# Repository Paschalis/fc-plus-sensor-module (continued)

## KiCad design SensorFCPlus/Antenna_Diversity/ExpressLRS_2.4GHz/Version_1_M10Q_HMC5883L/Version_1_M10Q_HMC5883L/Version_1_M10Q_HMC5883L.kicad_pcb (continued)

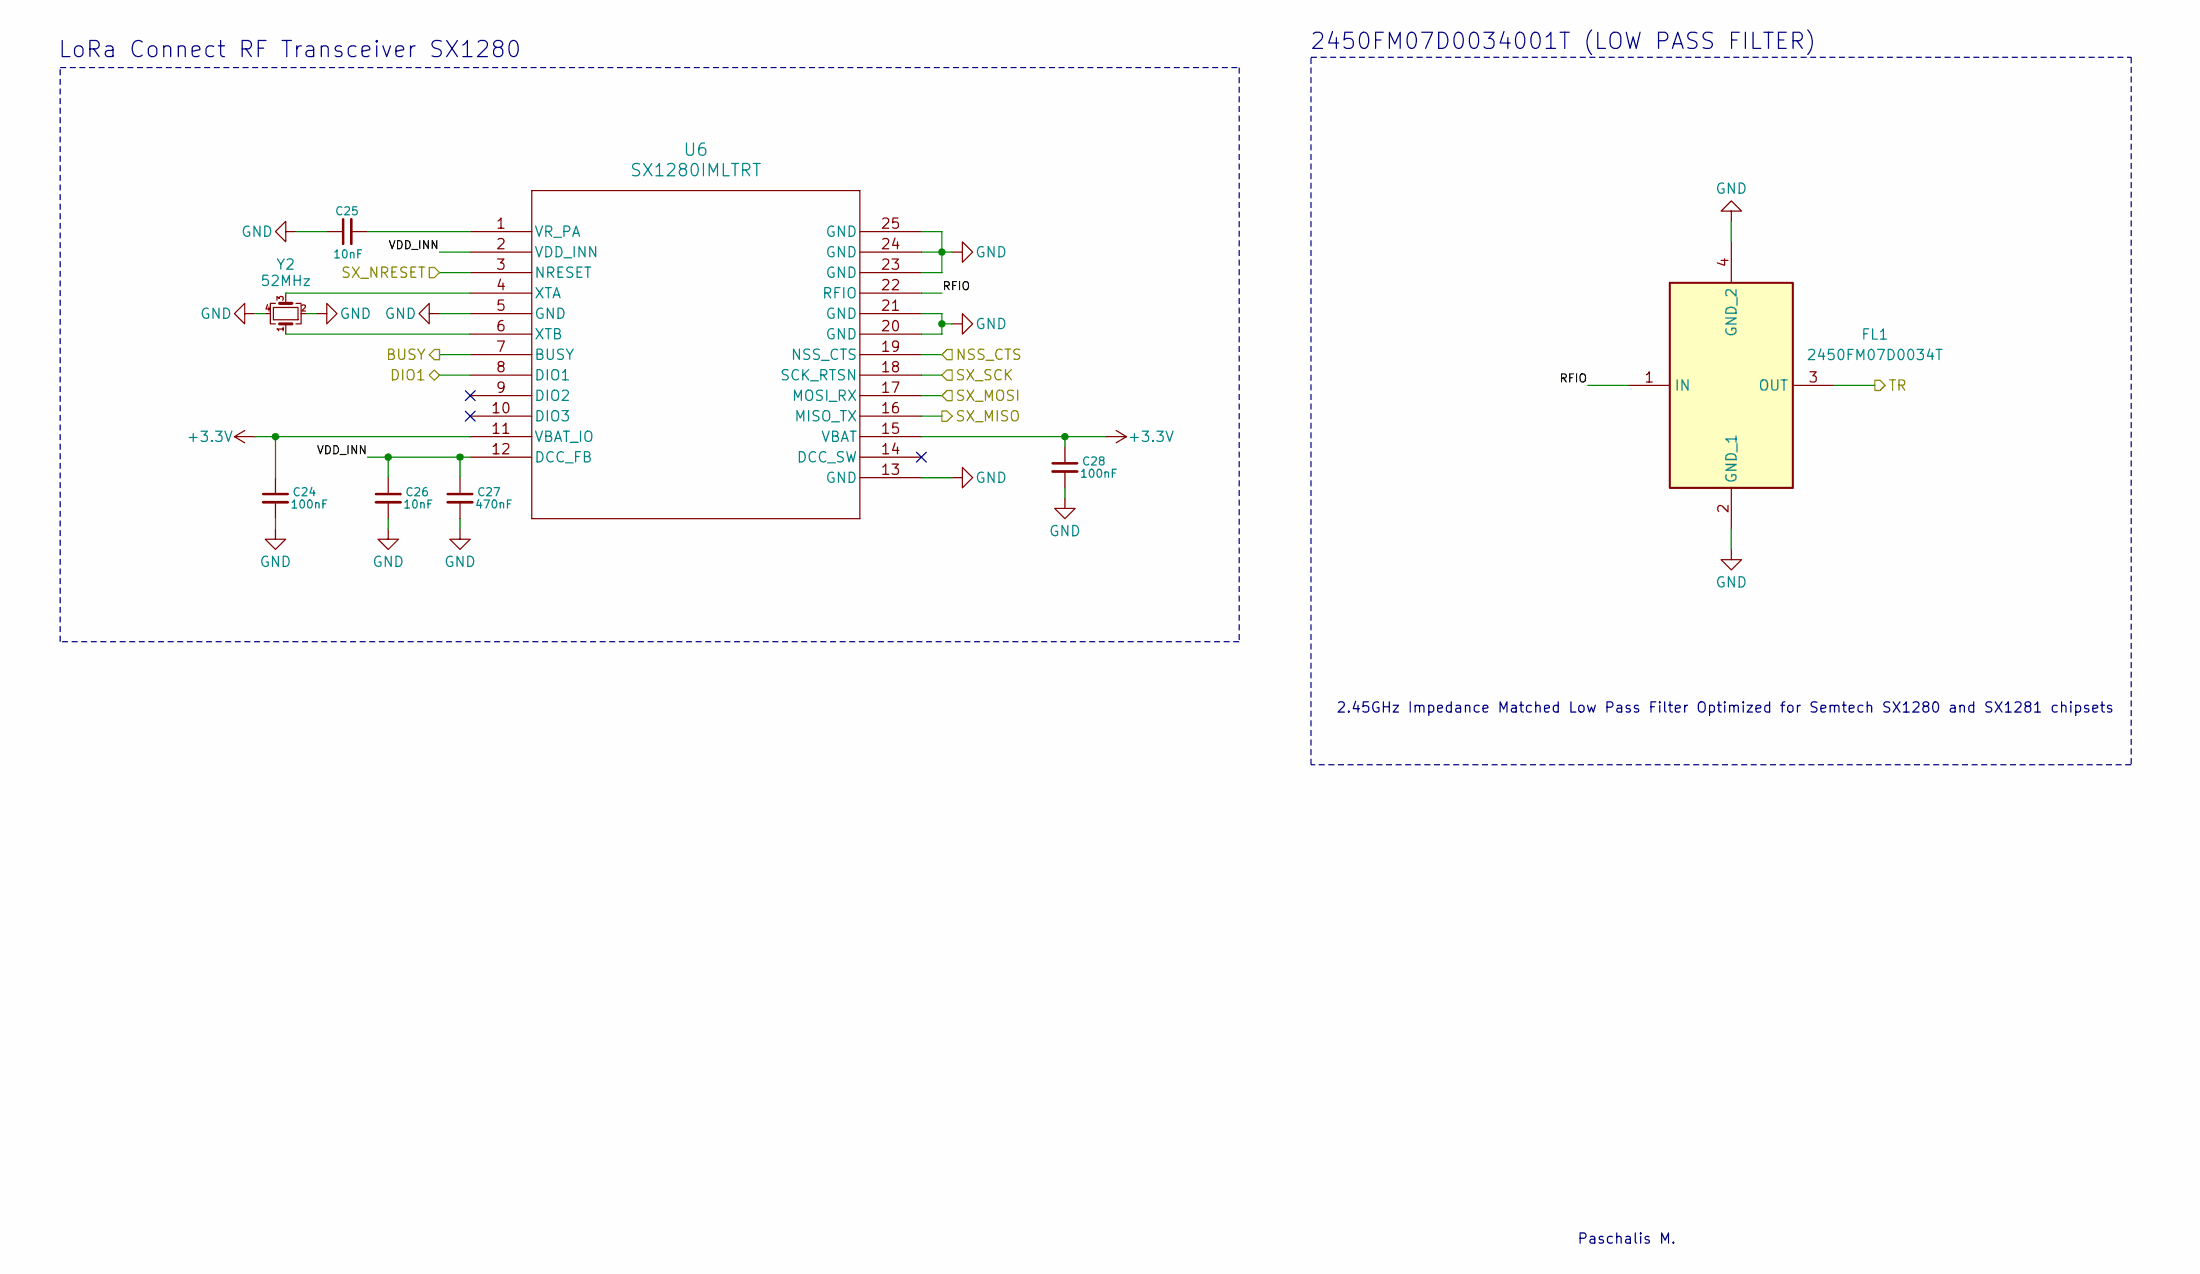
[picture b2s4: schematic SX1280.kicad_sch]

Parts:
C24, C28: 100nF; C_0805_2012Metric_Pad1.18x1.45mm_HandSolder
C25, C26: 10nF; C_0805_2012Metric_Pad1.18x1.45mm_HandSolder
C27: 470nF; C_0805_2012Metric_Pad1.18x1.45mm_HandSolder
FL1: 2450FM07D0034T; Mouser Part Number 609-2450FM07D0034T
U6: SX1280IMLTRT; QFN24_4X4_SEM
Y2: 52MHz; Crystal_SMD_2016-4Pin_2.0x1.6mm

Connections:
+3.3V: C24.1, C28.1, U6.11 (VBAT_IO), U6.15 (VBAT); also elsewhere on the board
/ESP8285/BUSY: U6.7 (BUSY); also elsewhere on the board
/ESP8285/DIO1: U6.8 (DIO1); also elsewhere on the board
/ESP8285/NSS_CTS: U6.19 (NSS_CTS); also elsewhere on the board
/ESP8285/SX_MISO: U6.16 (MISO_TX); also elsewhere on the board
/ESP8285/SX_MOSI: U6.17 (MOSI_RX); also elsewhere on the board
/ESP8285/SX_NRESET: U6.3 (NRESET); also elsewhere on the board
/ESP8285/SX_SCK: U6.18 (SCK_RTSN); also elsewhere on the board
/SE2431L/TR: FL1.3 (OUT); also elsewhere on the board
/SX1280/RFIO: FL1.1 (IN), U6.22 (RFIO)
/SX1280/VDD_INN: C26.1, C27.1, U6.2 (VDD_INN), U6.12 (DCC_FB)
GND: C24.2, C25.1, C26.2, C27.2, C28.2, FL1.2 (GND_1), FL1.4 (GND_2), U6.5 (GND), U6.13 (GND), U6.20 (GND), U6.21 (GND), U6.23 (GND), U6.24 (GND), U6.25 (GND), Y2.2, Y2.4; also elsewhere on the board
unnamed: C25.2, U6.1 (VR_PA)
unnamed: U6.4 (XTA), Y2.3
unnamed: U6.6 (XTB), Y2.1

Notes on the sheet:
2450FM07D0034001T (LOW PASS FILTER)
LoRa Connect RF Transceiver SX1280
Paschalis M.
2.45GHz Impedance Matched Low Pass Filter Optimized for Semtech SX1280 and SX1281 chipsets

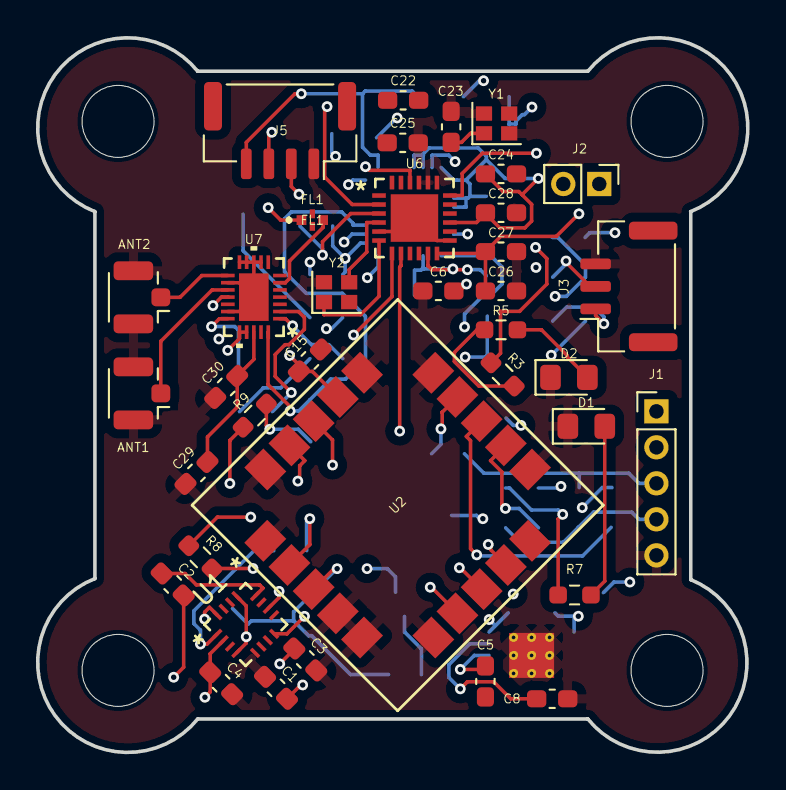
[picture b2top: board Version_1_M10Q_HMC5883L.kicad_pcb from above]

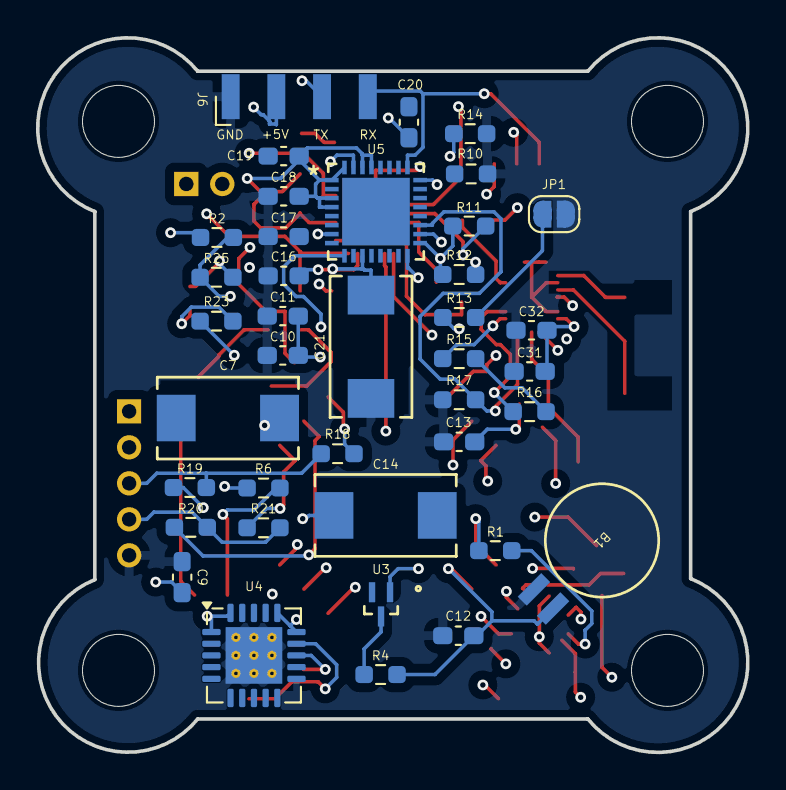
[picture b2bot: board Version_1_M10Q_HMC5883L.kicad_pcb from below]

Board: 4 copper layers, 39.4 x 39.7 mm, 80 parts (39 on the bottom side), 57 nets.

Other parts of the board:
hole1, hole2, hole3, hole4: MountingHole_4mm

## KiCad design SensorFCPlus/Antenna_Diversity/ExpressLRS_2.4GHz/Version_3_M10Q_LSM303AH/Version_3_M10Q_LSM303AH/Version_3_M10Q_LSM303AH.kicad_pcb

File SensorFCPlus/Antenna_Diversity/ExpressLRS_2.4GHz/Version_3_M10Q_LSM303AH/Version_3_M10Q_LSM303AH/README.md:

<div align="center">

# V3-M10Q-LSM

Antenna Diversity 
(GPS: SAM-M10Q, MAG: LSM303AH, ELRS:2.4GHz_RX)

</div>

## Bill of Materials

| **Reference**   | **Value**          | **Datasheet** | **Footprint**                                             | **Qty** | **DNP** |
|------------------|--------------------|---------------|----------------------------------------------------------|---------|---------|
| **AE1**         | Antenna            | ~             | RF_Antenna:Texas_SWRA117D_2.4GHz_Right                   | 1       |         |
| **ANT1, ANT2**  | Conn_Coaxial       | ~             | Connector_Coaxial:U.FL_Hirose_U.FL-R-SMT-1_Vertical      | 2       |         |
| **B1**          | MS621FEFL11E       | MS621FEFL11E  | MS621FE-FL11E:MS621FE-FL11E                              | 1       |         |
| **C1**          | 220nF             | ~             | Capacitor_SMD:C_0603_1608Metric_Pad1.08x0.95mm_HandSolder| 1       |         |
| **C2, C6, C9, C13, C21** | 10uF   | ~             | -- mixed values --                                       | 5       |         |
| **C3, C4, C5, C7, C8, C12** | 0.1uF | ~            | -- mixed values --                                       | 6       |         |
| **C10**         | 1uF               | ~             | Capacitor_SMD:C_0805_2012Metric_Pad1.18x1.45mm_HandSolder| 1       |         |
| **C11**         | 47uF              | ~             | Capacitor_SMD:C_0805_2012Metric_Pad1.18x1.45mm_HandSolder| 1       |         |
| **C14–C20, C24, C28, C31** | 100nF | ~            | -- mixed values --                                       | 10      |         |
| **C22, C23, C29, C30** | 10pF       | ~             | -- mixed values --                                       | 4       |         |
| **C25, C26**    | 10nF              | ~             | Capacitor_SMD:C_0603_1608Metric_Pad1.08x0.95mm_HandSolder| 2       |         |
| **C27**         | 470nF             | ~             | Capacitor_SMD:C_0603_1608Metric_Pad1.08x0.95mm_HandSolder| 1       |         |
| **C32**         | 2.2uF             | ~             | Capacitor_SMD:C_0603_1608Metric_Pad1.08x0.95mm_HandSolder| 1       |         |
| **D1, D2**      | LED               | ~             | LED_SMD:LED_0805_2012Metric_Pad1.15x1.40mm_HandSolder    | 2       |         |
| **FL1**         | 2450FM07D0034T    | [Datasheet](https://www.mouser.co.uk/datasheet/2/611/2450FM07D0034-1375634.pdf) | 2450FM07D0034T:2450FM07D0034T | 1 | |
| **J1, J3**      | Conn_01x05_Pin    | ~             | Connector_PinHeader_2.00mm:PinHeader_1x05_P2.00mm_Vertical| 2       |         |
| **J2**          | Conn_01x02_Pin    | ~             | Connector_PinHeader_2.00mm:PinHeader_1x02_P2.00mm_Vertical| 1       |         |
| **J4**          | Conn_01x03_Pin    | ~             | Connector_PinHeader_2.00mm:PinHeader_1x03_P2.00mm_Vertical| 1       |         |
| **J5**          | Conn_01x04_Pin    | ~             | Connector_JST:JST_GH_SM04B-GHS-TB_1x04-1MP_P1.25mm_Horizontal| 1    |         |
| **J6**          | Conn_01x04_Socket | ~             | Connector_Harwin:Harwin_M20-89004xx_1x04_P2.54mm_Horizontal| 1      |         |
| **JP1**         | Jumper_2_Bridged  | ~             | Jumper:SolderJumper-2_P1.3mm_Open_RoundedPad1.0x1.5mm     | 1       |         |
| **R1, R5, R16** | 1K                | ~             | -- mixed values --                                       | 3       |         |
| **R2, R3**      | 1.5K              | ~             | Resistor_SMD:R_0805_2012Metric_Pad1.20x1.40mm_HandSolder | 2       |         |
| **R4**          | 4.7K              | ~             | Resistor_SMD:R_0805_2012Metric_Pad1.20x1.40mm_HandSolder | 1       |         |
| **R6–R15**      | 0                 | ~             | -- mixed values --                                       | 10      |         |
| **R17–R20, R22**| 10K               | ~             | -- mixed values --                                       | 5       |         |
| **R21**         | 12K               | ~             | Resistor_SMD:R_0603_1608Metric_Pad0.98x0.95mm_HandSolder | 1       |         |
| **R23**         | 2.2K              | ~             | Resistor_SMD:R_0603_1608Metric_Pad0.98x0.95mm_HandSolder | 1       |         |
| **R24**         | 1.2K              | ~             | Resistor_SMD:R_0603_1608Metric_Pad0.98x0.95mm_HandSolder | 1       |         |
| **U1**          | LSM303AHTR        | LSM303AHTR    | LSM303AHTR:LSM303AHTR                                    | 1       |         |
| **U2**          | SAM-M10Q-00B      | SAM-M10Q-00B  | SAM-M10Q-00B:SAM-M10Q_UBL                                 | 1       |         |
| **U3**          | BAT54STA          | BAT54STA      | SOT23_BAT54STA_1P7XP85_DIO                                | 1       |         |
| **U4**          | TPS7A4701xRGW     | [Datasheet](https://www.ti.com/lit/ds/symlink/tps7a47.pdf) | Package_DFN_QFN:Texas_RGW0020A_VQFN-20-1EP_5x5mm | 1  | |
| **U5**          | ESP8285H16        | ESP8285H16    | ESP8285H16:QFN32_5X5_EXP                                  | 1       |         |
| **U6**          | SX1280IMLTRT      | SX1280IMLTRT  | SX1280IMLTRT:QFN24_4X4_SEM                                | 1       |         |
| **U7**          | SE2431L-R         | SE2431L-R     | SE2431L-R:SE2431L_SKY                                     | 1       |         |
| **Y1**          | 26MHz             | ~             | Crystal:Crystal_SMD_2016-4Pin_2.0x1.6mm                   | 1       |         |
| **Y2**          | 52MHz             | ~             | Crystal:Crystal_SMD_2016-4Pin_2.0x1.6mm                   | 1       |         |

[⬅️ Go Back to Main README](https://github.com/Paschalis/fc-plus-sensor-module)

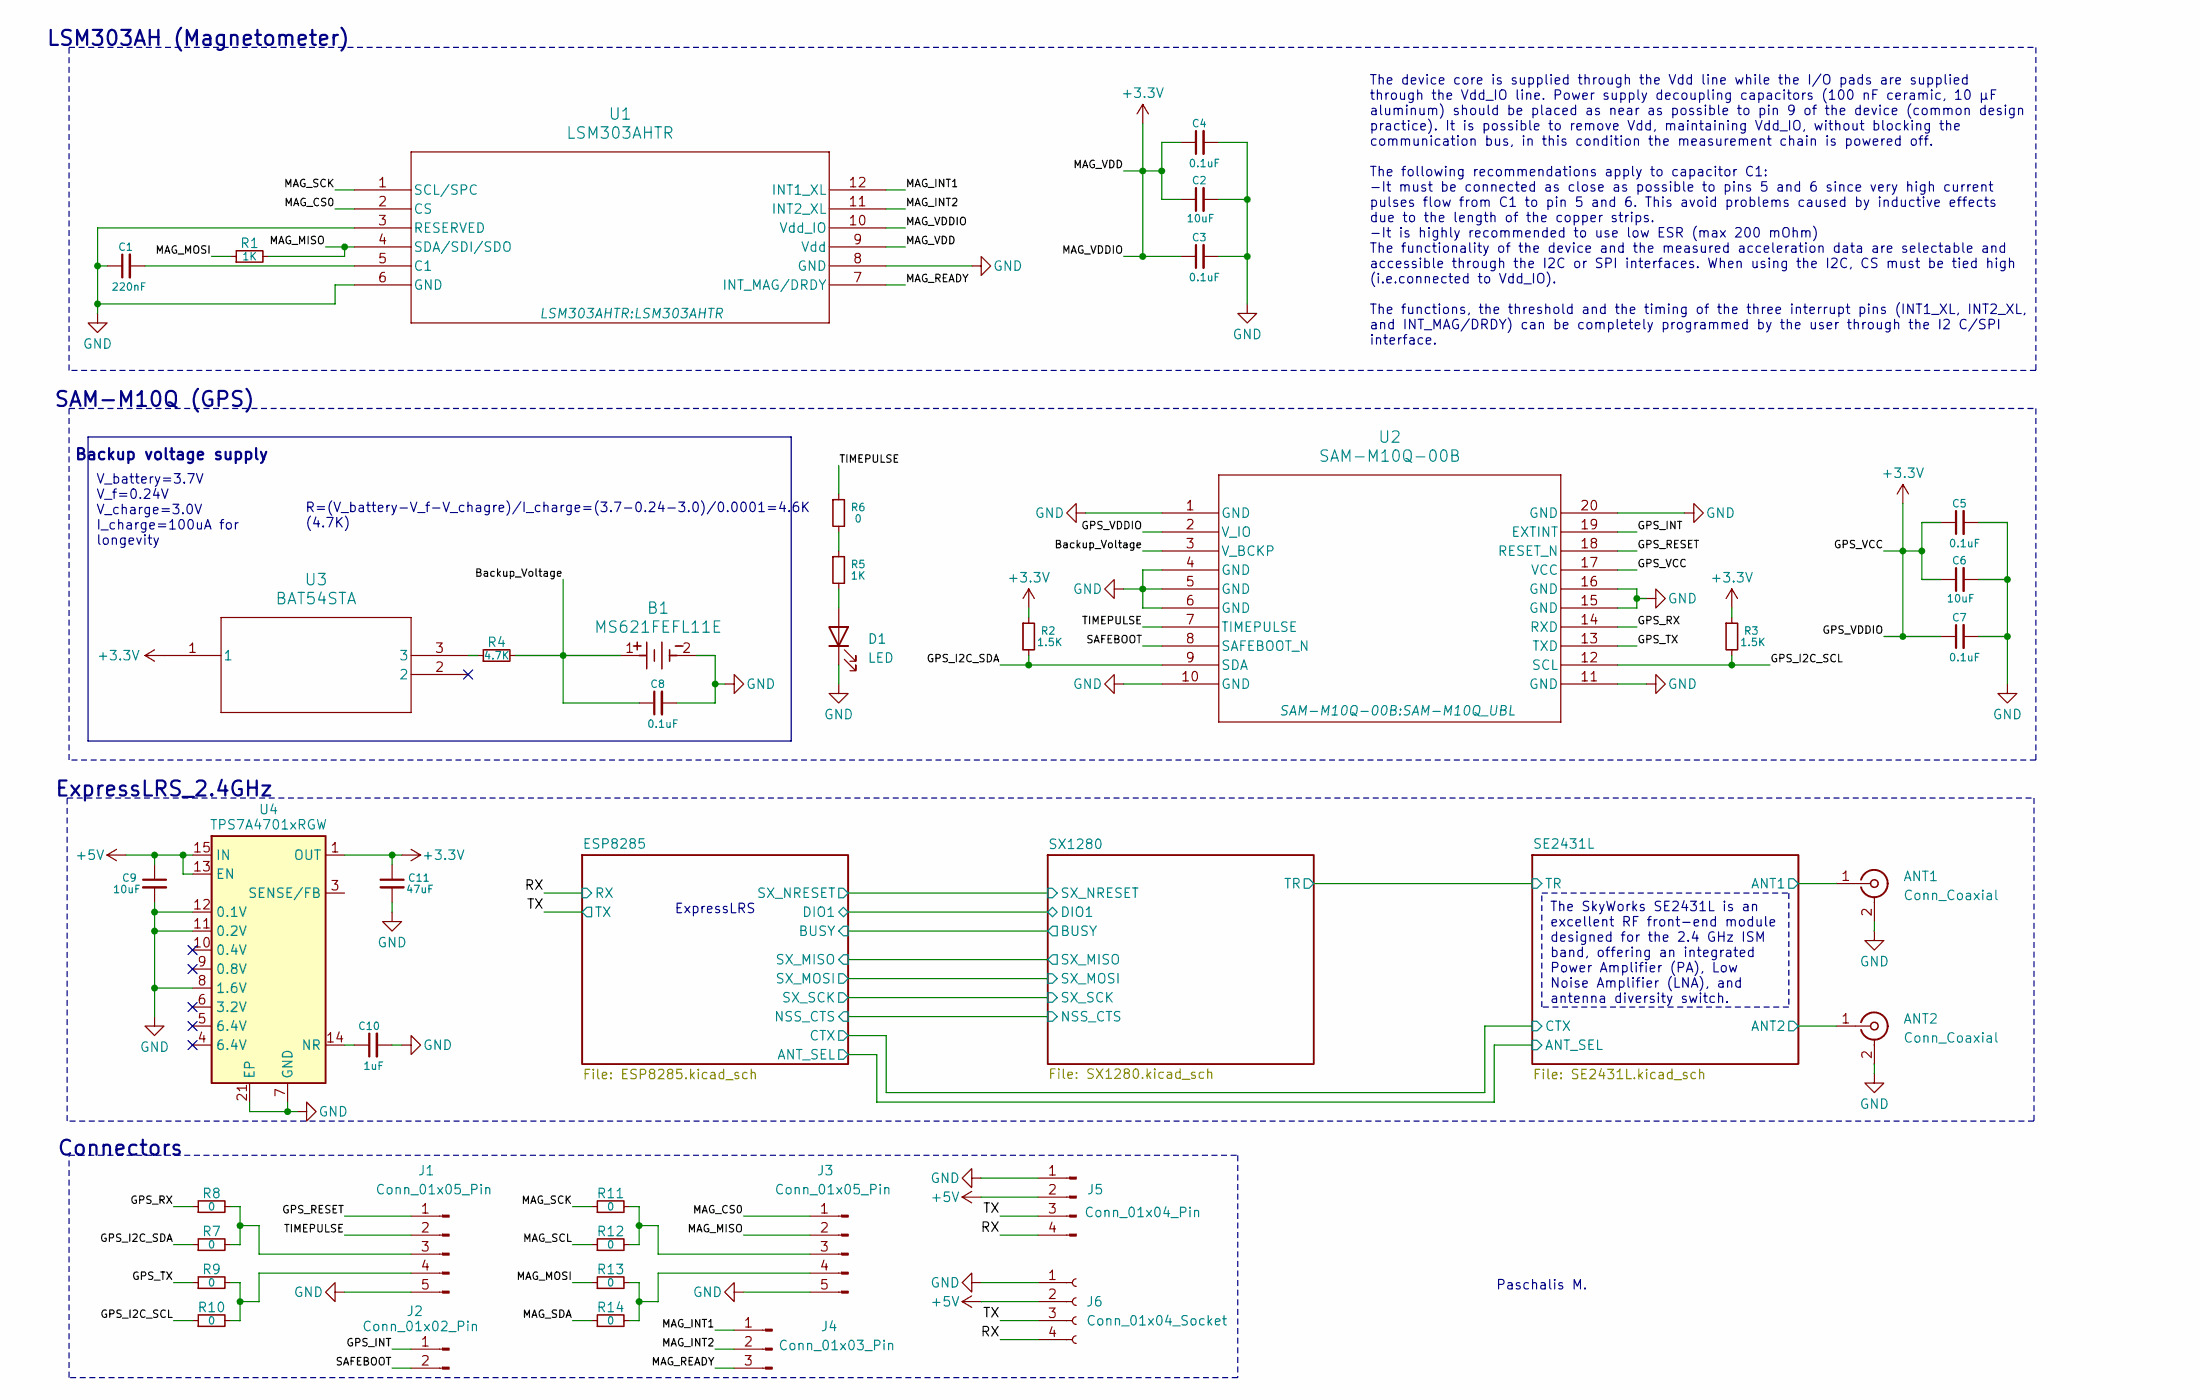
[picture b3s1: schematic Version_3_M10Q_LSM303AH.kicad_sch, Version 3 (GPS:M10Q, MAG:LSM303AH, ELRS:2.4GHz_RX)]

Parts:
ANT1, ANT2: Conn_Coaxial; U.FL_Hirose_U.FL-R-SMT-1_Vertical
B1: MS621FEFL11E; MS621FE-FL11E
C1: 220nF; C_0603_1608Metric_Pad1.08x0.95mm_HandSolder
C2, C6: 10uF; ECASD40J106M055K00
C3, C4: 0.1uF; C_0603_1608Metric_Pad1.08x0.95mm_HandSolder
C5, C7, C8: 0.1uF; C_0805_2012Metric_Pad1.18x1.45mm_HandSolder
C9: 10uF; C_0805_2012Metric_Pad1.18x1.45mm_HandSolder
C10: 1uF; C_0805_2012Metric_Pad1.18x1.45mm_HandSolder
C11: 47uF; C_0805_2012Metric_Pad1.18x1.45mm_HandSolder
D1: LED; LED_0805_2012Metric_Pad1.15x1.40mm_HandSolder
J1, J3: Conn_01x05_Pin; PinHeader_1x05_P2.00mm_Vertical
J2: Conn_01x02_Pin; PinHeader_1x02_P2.00mm_Vertical
J4: Conn_01x03_Pin; PinHeader_1x03_P2.00mm_Vertical
J5: Conn_01x04_Pin; JST_GH_SM04B-GHS-TB_1x04-1MP_P1.25mm_Horizontal
J6: Conn_01x04_Socket; Harwin_M20-89004xx_1x04_P2.54mm_Horizontal
R1: 1K; R_0603_1608Metric_Pad0.98x0.95mm_HandSolder
R2, R3: 1.5K; R_0805_2012Metric_Pad1.20x1.40mm_HandSolder
R4: 4.7K; R_0805_2012Metric_Pad1.20x1.40mm_HandSolder
R5: 1K; R_0805_2012Metric_Pad1.20x1.40mm_HandSolder
R6: 0; R_0805_2012Metric_Pad1.20x1.40mm_HandSolder
R7, R8, R9, R10, R11, R12, R13, R14: 0; R_0603_1608Metric_Pad0.98x0.95mm_HandSolder
U1: LSM303AHTR
U2: SAM-M10Q-00B; SAM-M10Q_UBL
U3: BAT54STA; SOT23_BAT54STA_1P7XP85_DIO
U4: TPS7A4701xRGW; Texas_RGW0020A_VQFN-20-1EP_5x5mm_P0.65mm_EP3.15x3.15mm_Ther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

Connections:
+3.3V: C2.1, C3.1, C4.1, C5.1, C6.1, C7.1, C11.1, R2.1, R3.1, U1.9 (Vdd), U1.10 (Vdd_IO), U2.2 (V_IO), U2.17 (VCC), U3.1, U4.1 (OUT), U4.20 (OUT); also elsewhere on the board
+5V: C9.1, J5.2, J6.2, U4.13 (EN), U4.15 (IN), U4.16 (IN)
/Backup_Voltage: B1.1, C8.1, R4.2, U2.3 (V_BCKP)
/GPS_I2C_SCL: R3.2, R10.1, U2.12 (SCL)
/GPS_I2C_SDA: R2.2, R7.1, U2.9 (SDA)
/GPS_INT: J2.1, U2.19 (EXTINT)
/GPS_RESET: J1.1, U2.18 (RESET_N)
/GPS_RX: R8.1, U2.14 (RXD)
/GPS_TX: R9.1, U2.13 (TXD)
/MAG_CS0: J3.1, U1.2 (CS)
/MAG_INT1: J4.1, U1.12 (INT1_XL)
/MAG_INT2: J4.2, U1.11 (INT2_XL)
/MAG_MISO: J3.2, R1.2, U1.4 (SDA/SDI/SDO)
/MAG_MOSI: R1.1, R13.1
/MAG_READY: J4.3, U1.7 (INT_MAG/DRDY)
/MAG_SCK: R11.1, U1.1 (SCL/SPC)
/MAG_SCL: R12.1
/MAG_SDA: R14.1
/RX: J5.4, J6.4; also elsewhere on the board
/SAFEBOOT: J2.2, U2.8 (SAFEBOOT_N)
/SE2431L/ANT1: ANT1.1 (In); also elsewhere on the board
/SE2431L/ANT2: ANT2.1 (In); also elsewhere on the board
/TIMEPULSE: J1.2, R6.1, U2.7 (TIMEPULSE)
/TX: J5.3, J6.3; also elsewhere on the board
GND: ANT1.2 (Ext), ANT2.2 (Ext), B1.2, C1.1, C2.2, C3.2, C4.2, C5.2, C6.2, C7.2, C8.2, C9.2, C10.2, C11.2, D1.1 (K), J1.5, J3.5, J5.1, J6.1, U1.3 (RESERVED), U1.6 (GND), U1.8 (GND), U2.1 (GND), U2.4 (GND), U2.5 (GND), U2.6 (GND), U2.10 (GND), U2.11 (GND), U2.15 (GND), U2.16 (GND), U2.20 (GND), U4.7 (GND), U4.8 (1.6V), U4.11 (0.2V), U4.12 (0.1V), U4.21 (EP); also elsewhere on the board
unnamed: D1.2 (A), R5.2
unnamed: J1.3, R7.2, R8.2
unnamed: J1.4, R9.2, R10.2
unnamed: J3.3, R11.2, R12.2
unnamed: J3.4, R13.2, R14.2
unnamed: R4.1, U3.3
unnamed: R5.1, R6.2
unnamed: C1.2, U1.5 (C1)
unnamed: C10.1, U4.14 (NR)

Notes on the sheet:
R=(V_battery-V_f-V_chagre)/I_charge=(3.7-0.24-3.0)/0.0001=4.6K (4.7K)
The SkyWorks SE2431L is an excellent RF front-end module designed for the 2.4 GHz ISM band, offering an integrated Power Amplifier (PA), Low Noise Amplifier (LNA), and antenna diversity switch.
V_battery=3.7V V_f=0.24V V_charge=3.0V I_charge=100uA for longevity
The device core is supplied through the Vdd line while the I/O pads are supplied through the Vdd_IO line. Power supply decoupling capacitors (100 nF ceramic, 10 μF aluminum) should be placed as near as possible to pin 9 of the device (common design practice). It is possible to remove Vdd, maintaini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
SAM-M10Q (GPS)
LSM303AH (Magnetometer)
Backup voltage supply
Paschalis M.
Connectors
ExpressLRS
ExpressLRS_2.4GHz

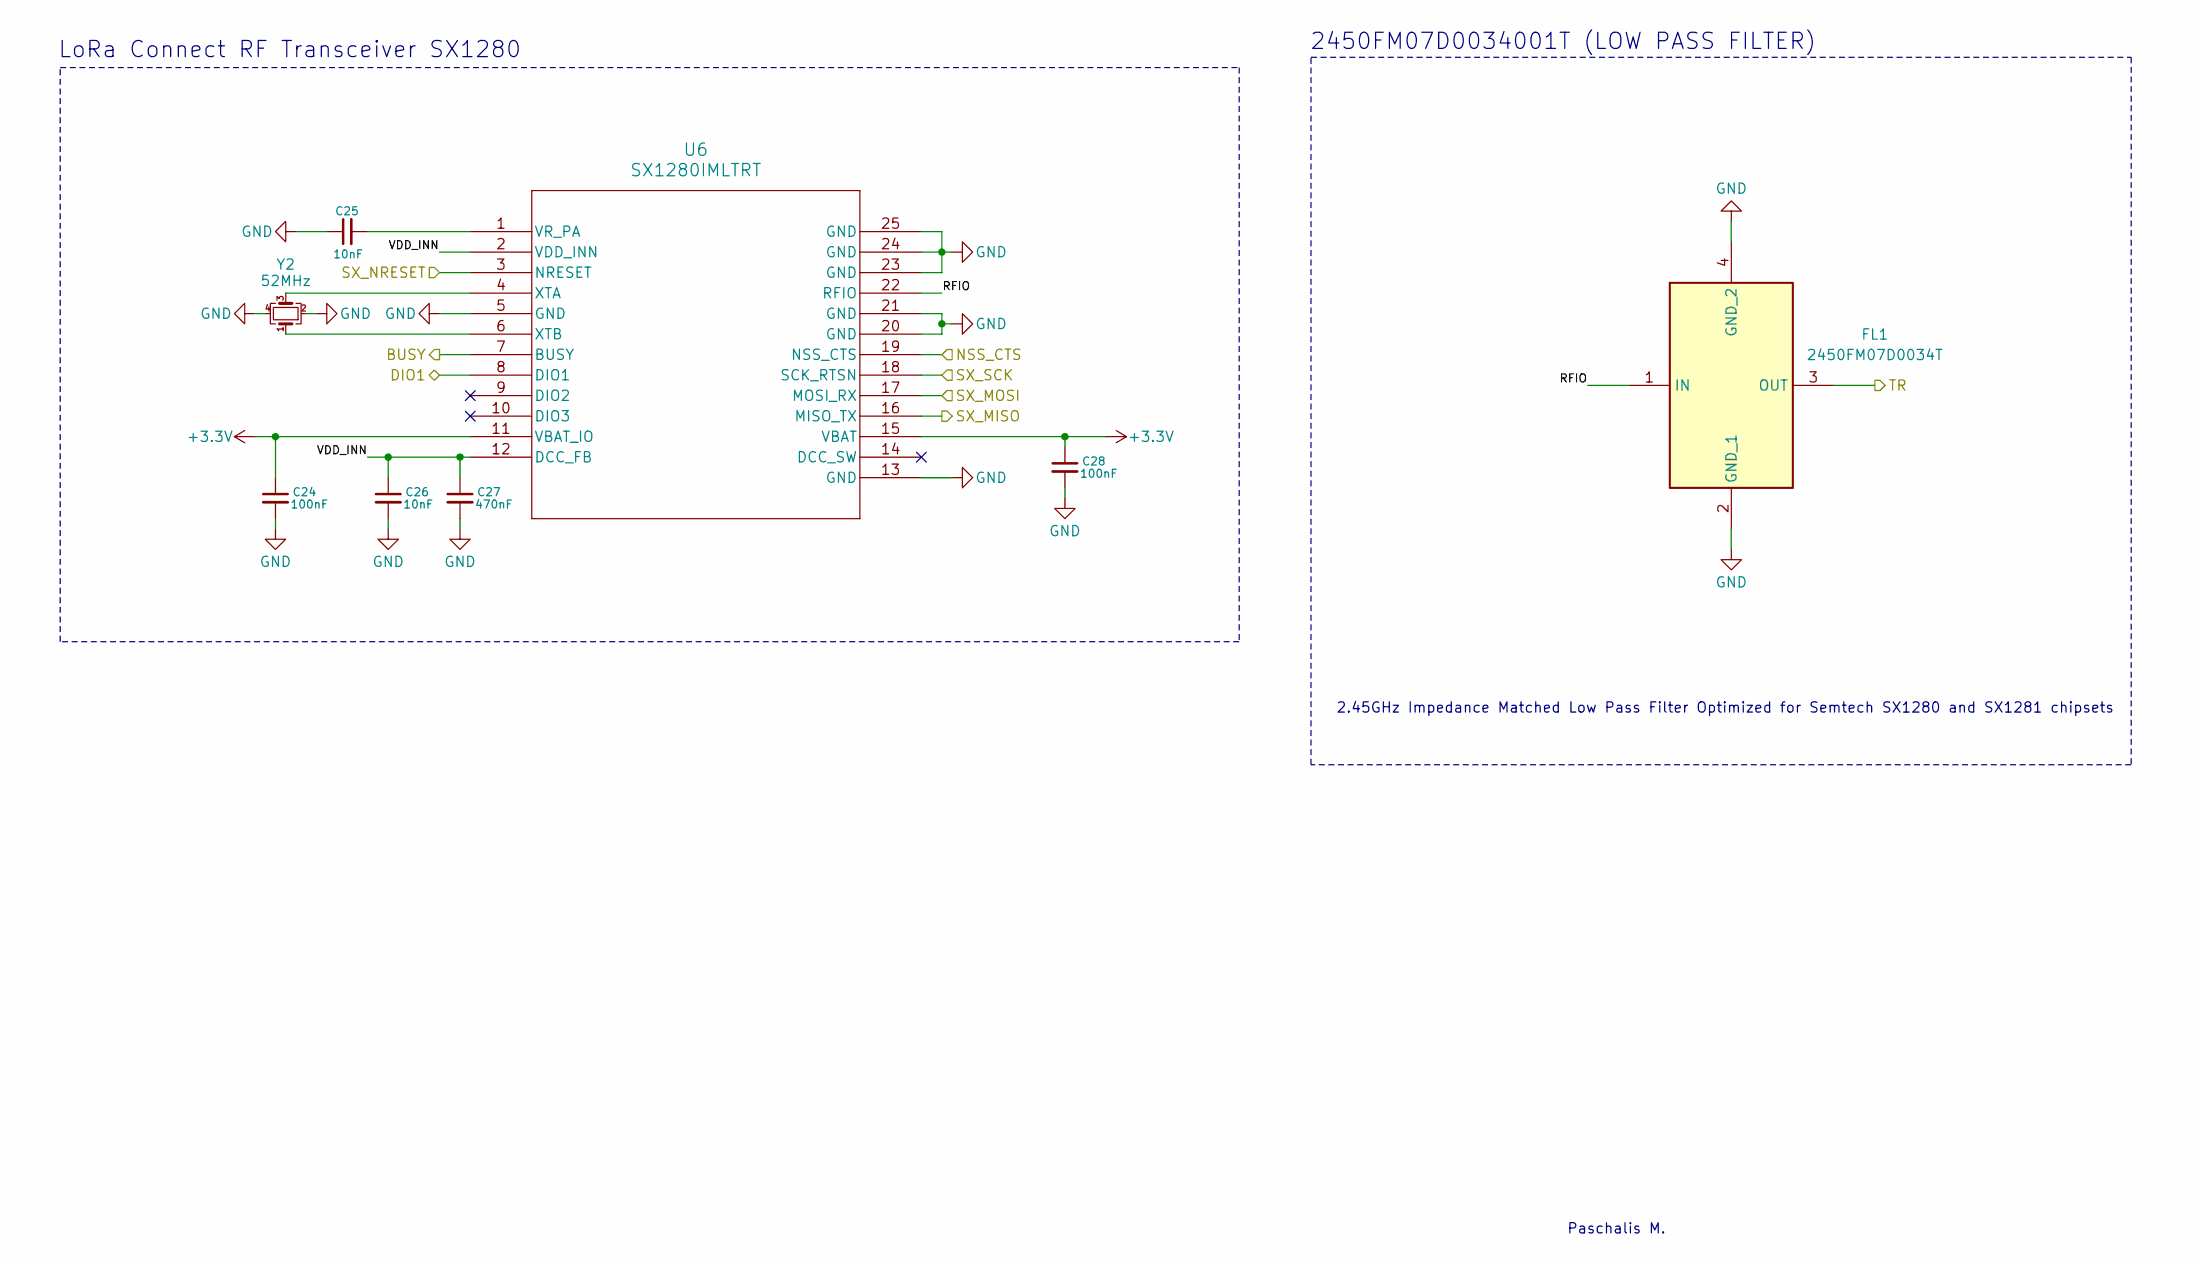
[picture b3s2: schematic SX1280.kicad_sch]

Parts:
C24, C28: 100nF; C_0603_1608Metric_Pad1.08x0.95mm_HandSolder
C25, C26: 10nF; C_0603_1608Metric_Pad1.08x0.95mm_HandSolder
C27: 470nF; C_0603_1608Metric_Pad1.08x0.95mm_HandSolder
FL1: 2450FM07D0034T; Mouser Part Number 609-2450FM07D0034T
U6: SX1280IMLTRT; QFN24_4X4_SEM
Y2: 52MHz; Crystal_SMD_2016-4Pin_2.0x1.6mm

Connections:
+3.3V: C24.1, C28.1, U6.11 (VBAT_IO), U6.15 (VBAT); also elsewhere on the board
/ESP8285/BUSY: U6.7 (BUSY); also elsewhere on the board
/ESP8285/DIO1: U6.8 (DIO1); also elsewhere on the board
/ESP8285/NSS_CTS: U6.19 (NSS_CTS); also elsewhere on the board
/ESP8285/SX_MISO: U6.16 (MISO_TX); also elsewhere on the board
/ESP8285/SX_MOSI: U6.17 (MOSI_RX); also elsewhere on the board
/ESP8285/SX_NRESET: U6.3 (NRESET); also elsewhere on the board
/ESP8285/SX_SCK: U6.18 (SCK_RTSN); also elsewhere on the board
/SE2431L/TR: FL1.3 (OUT); also elsewhere on the board
/SX1280/RFIO: FL1.1 (IN), U6.22 (RFIO)
/SX1280/VDD_INN: C26.1, C27.1, U6.2 (VDD_INN), U6.12 (DCC_FB)
GND: C24.2, C25.1, C26.2, C27.2, C28.2, FL1.2 (GND_1), FL1.4 (GND_2), U6.5 (GND), U6.13 (GND), U6.20 (GND), U6.21 (GND), U6.23 (GND), U6.24 (GND), U6.25 (GND), Y2.2, Y2.4; also elsewhere on the board
unnamed: C25.2, U6.1 (VR_PA)
unnamed: U6.4 (XTA), Y2.3
unnamed: U6.6 (XTB), Y2.1

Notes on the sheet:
Paschalis M.
2.45GHz Impedance Matched Low Pass Filter Optimized for Semtech SX1280 and SX1281 chipsets
LoRa Connect RF Transceiver SX1280
2450FM07D0034001T (LOW PASS FILTER)

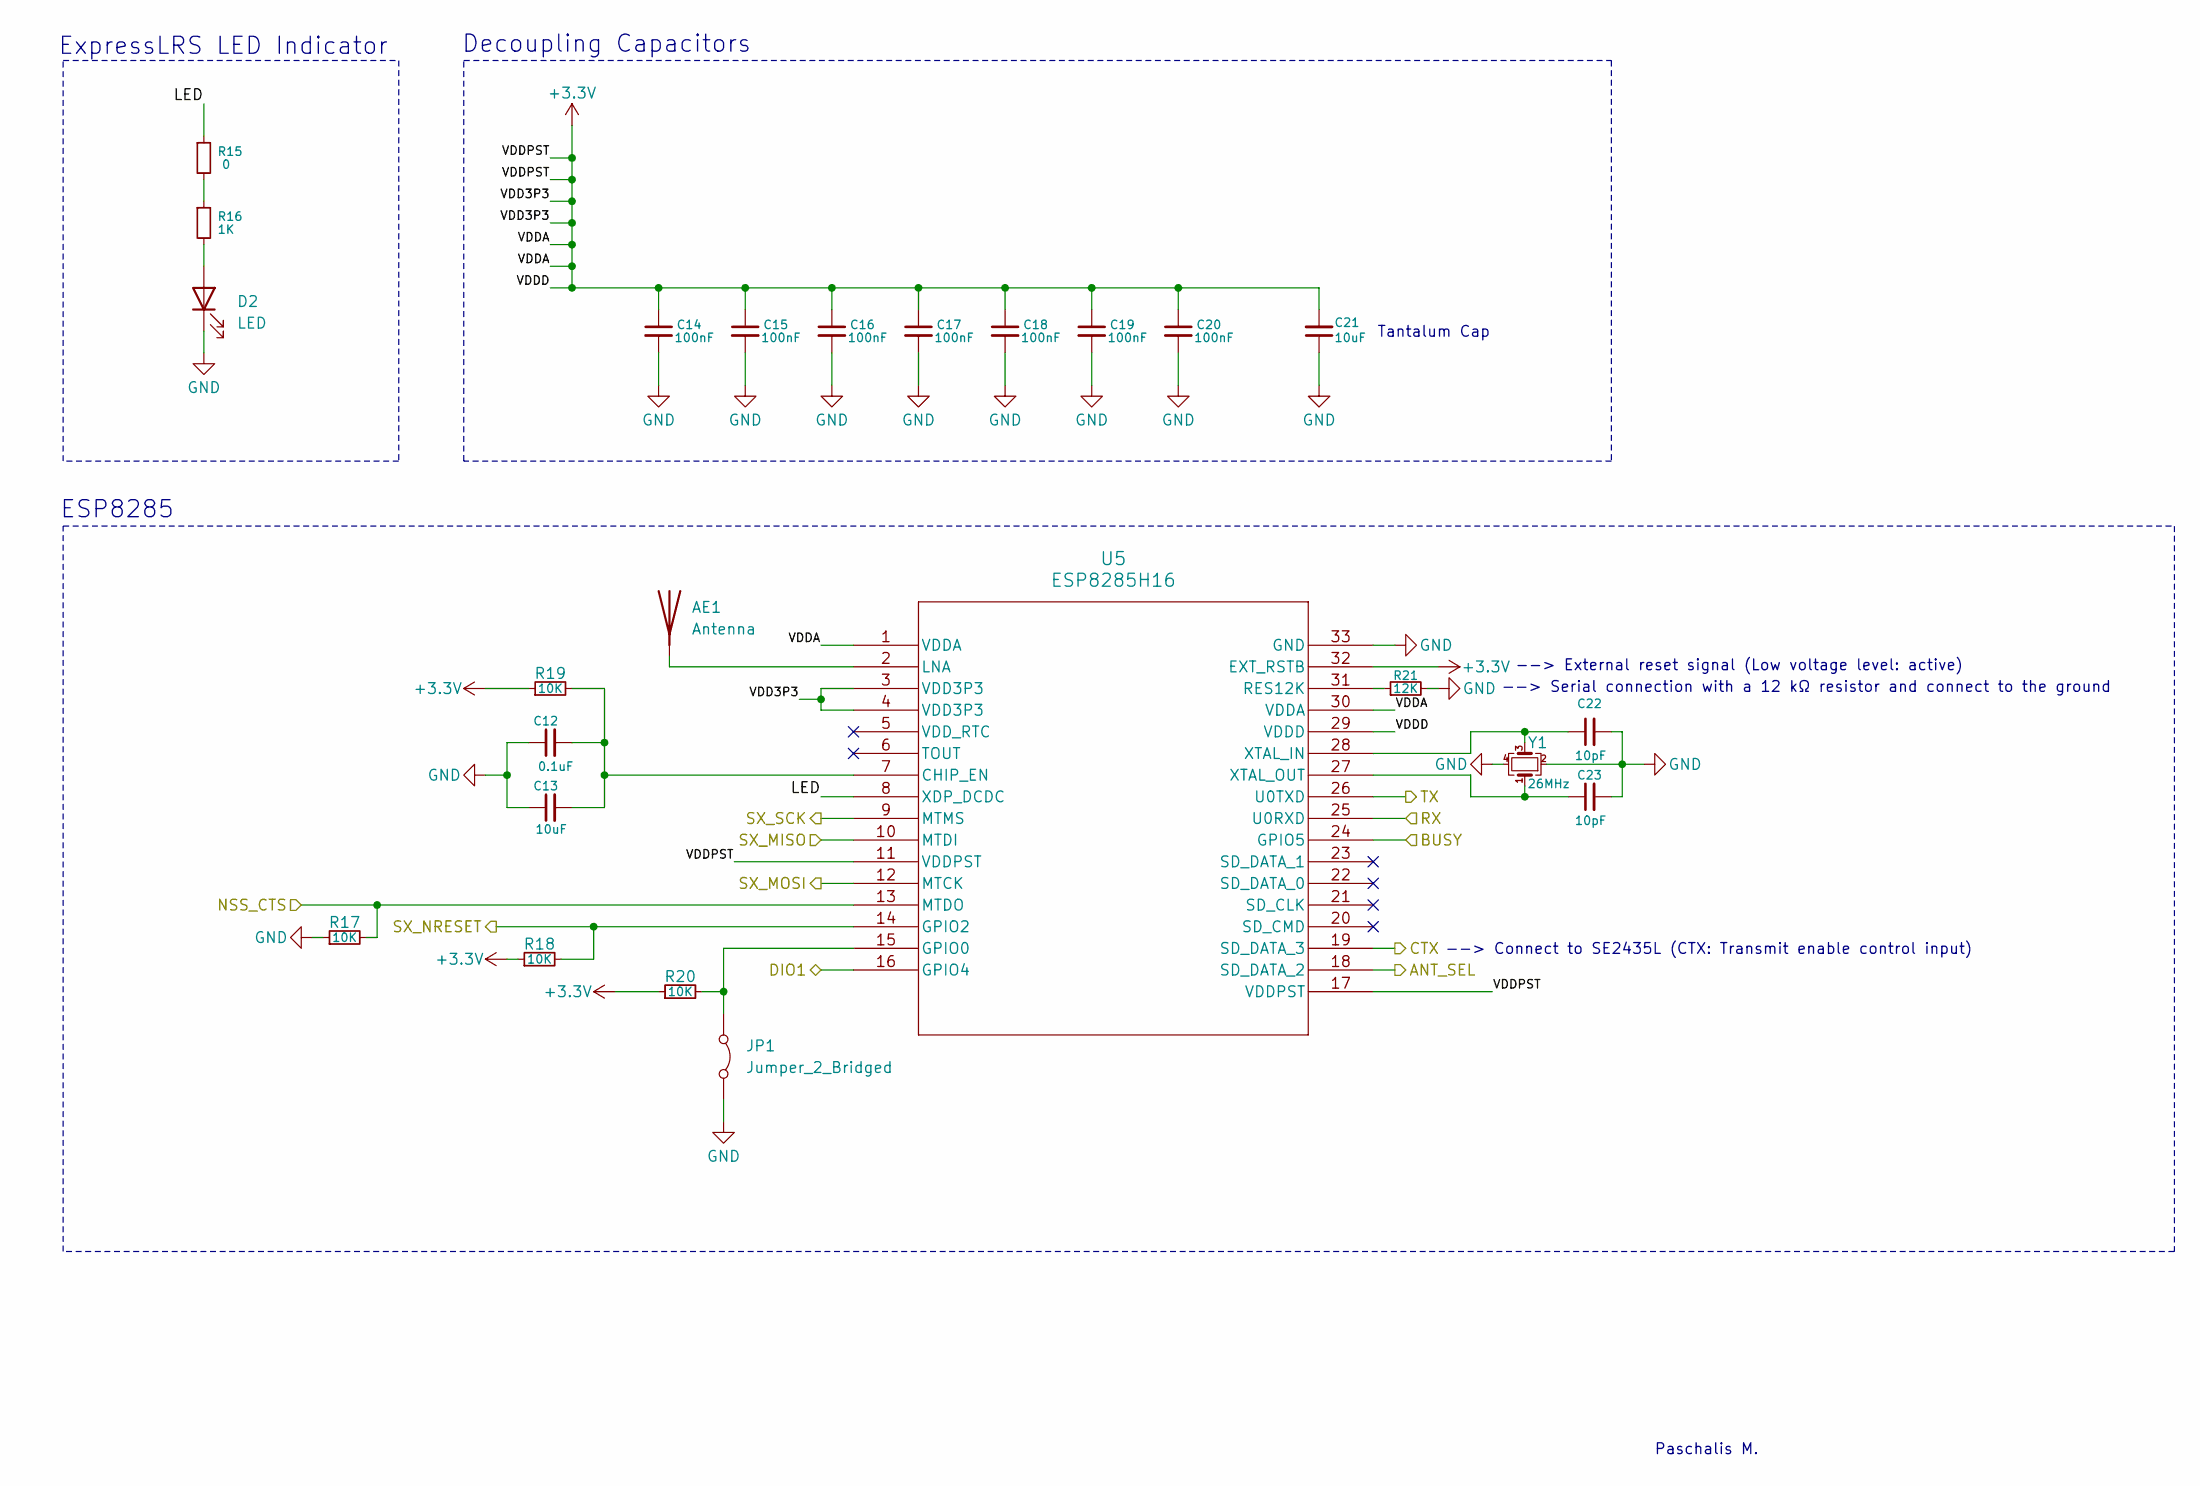
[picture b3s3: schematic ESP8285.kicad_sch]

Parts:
AE1: Antenna; Texas_SWRA117D_2.4GHz_Right
C12: 0.1uF; C_0603_1608Metric_Pad1.08x0.95mm_HandSolder
C13, C21: 10uF; ECASD40J106M055K00
C14, C15, C16, C17, C18, C19, C20: 100nF; C_0805_2012Metric_Pad1.18x1.45mm_HandSolder
C22, C23: 10pF; C_0805_2012Metric_Pad1.18x1.45mm_HandSolder
D2: LED; LED_0805_2012Metric_Pad1.15x1.40mm_HandSolder
JP1: Jumper_2_Bridged; SolderJumper-2_P1.3mm_Open_RoundedPad1.0x1.5mm
R15: 0; R_0805_2012Metric_Pad1.20x1.40mm_HandSolder
R16: 1K; R_0805_2012Metric_Pad1.20x1.40mm_HandSolder
R17, R18, R20: 10K; R_0603_1608Metric_Pad0.98x0.95mm_HandSolder
R19: 10K; R_0805_2012Metric_Pad1.20x1.40mm_HandSolder
R21: 12K; R_0603_1608Metric_Pad0.98x0.95mm_HandSolder
U5: ESP8285H16; QFN32_5X5_EXP
Y1: 26MHz; Crystal_SMD_2016-4Pin_2.0x1.6mm

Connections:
+3.3V: C14.1, C15.1, C16.1, C17.1, C18.1, C19.1, C20.1, C21.2, R18.1, R19.1, R20.1, U5.1 (VDDA), U5.3 (VDD3P3), U5.4 (VDD3P3), U5.11 (VDDPST), U5.17 (VDDPST), U5.29 (VDDD), U5.30 (VDDA), U5.32 (EXT_RSTB); also elsewhere on the board
/ESP8285/ANT_SEL: U5.18 (SD_DATA_2); also elsewhere on the board
/ESP8285/BUSY: U5.24 (GPIO5); also elsewhere on the board
/ESP8285/CTX: U5.19 (SD_DATA_3); also elsewhere on the board
/ESP8285/DIO1: U5.16 (GPIO4); also elsewhere on the board
/ESP8285/LED: R15.1, U5.8 (XDP_DCDC)
/ESP8285/NSS_CTS: R17.2, U5.13 (MTDO); also elsewhere on the board
/ESP8285/SX_MISO: U5.10 (MTDI); also elsewhere on the board
/ESP8285/SX_MOSI: U5.12 (MTCK); also elsewhere on the board
/ESP8285/SX_NRESET: R18.2, U5.14 (GPIO2); also elsewhere on the board
/ESP8285/SX_SCK: U5.9 (MTMS); also elsewhere on the board
/RX: U5.25 (U0RXD); also elsewhere on the board
/TX: U5.26 (U0TXD); also elsewhere on the board
GND: C12.1, C13.1, C14.2, C15.2, C16.2, C17.2, C18.2, C19.2, C20.2, C21.1, C22.2, C23.2, D2.1 (K), JP1.2 (B), R17.1, R21.2, U5.33 (GND), Y1.2, Y1.4; also elsewhere on the board
unnamed: AE1.1, U5.2 (LNA)
unnamed: D2.2 (A), R16.2
unnamed: JP1.1 (A), R20.2, U5.15 (GPIO0)
unnamed: R15.2, R16.1
unnamed: C12.2, C13.2, R19.2, U5.7 (CHIP_EN)
unnamed: R21.1, U5.31 (RES12K)
unnamed: C22.1, U5.28 (XTAL_IN), Y1.3
unnamed: C23.1, U5.27 (XTAL_OUT), Y1.1

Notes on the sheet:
--> External reset signal (Low voltage level: active)
Decoupling Capacitors
ExpressLRS LED Indicator
--> Connect to SE2435L (CTX: Transmit enable control input)
--> Serial connection with a 12 kΩ resistor and connect to the ground
Tantalum Cap
Paschalis M.
ESP8285
